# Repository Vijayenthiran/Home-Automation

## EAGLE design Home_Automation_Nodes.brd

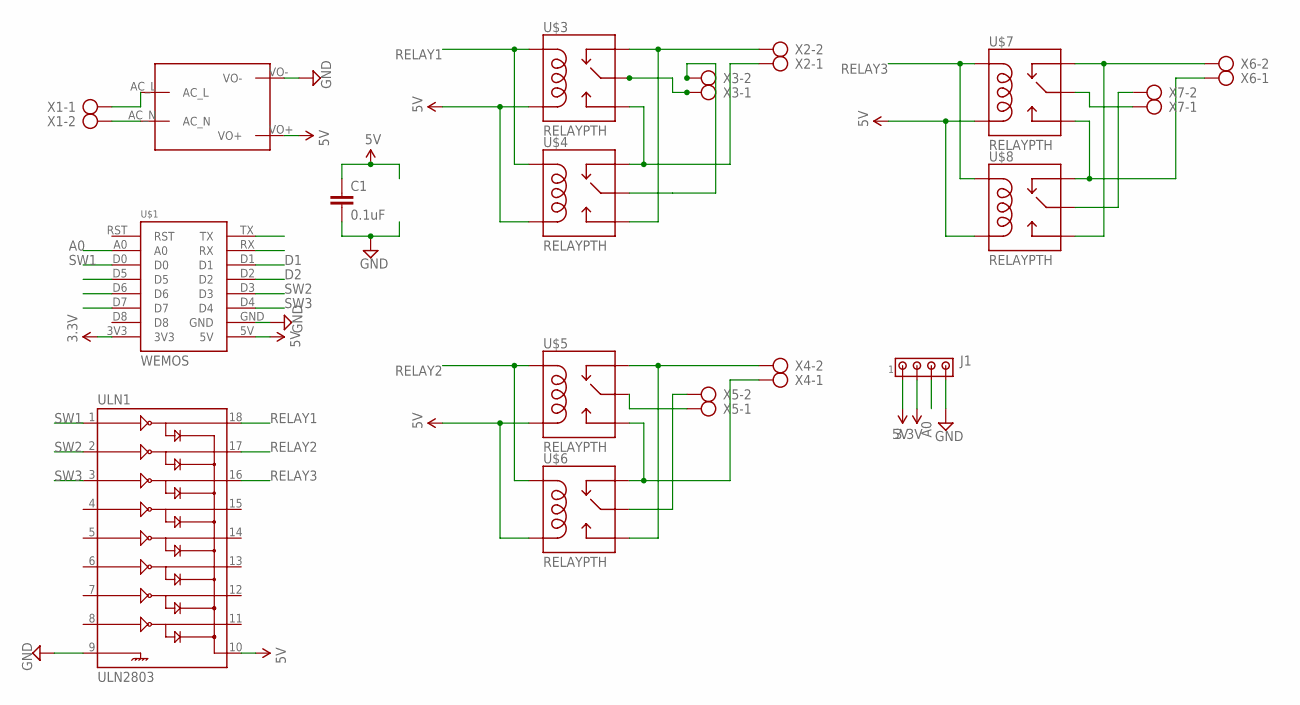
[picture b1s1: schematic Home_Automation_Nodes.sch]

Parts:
C1: 0.1uF; C025-025X050
J1: MTA04-100; 10X04MTA
U$1: WEMOS
U$2: MAINS_CONVERTERS; HLK-PM01
U$3, U$4, U$5, U$6, U$7, U$8: RELAYPTH; SRD-05VDC-SL-C
ULN1: ULN2803; DIL18
X1, X2, X3, X4, X5, X6, X7: AK300/2

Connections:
3.3V: J1.2, U$1.3V3
5V: C1.1, J1.1, U$1.5V, U$2.VO+, U$3.COIL0, U$4.COIL0, U$5.COIL0, U$6.COIL0, U$7.COIL0, U$8.COIL0, ULN1.10
A0: J1.3, U$1.A0
D1: U$1.D1
D2: U$1.D2
D5: U$1.D5
D6: U$1.D6
D7: U$1.D7
GND: C1.2, J1.4, U$1.GND, U$2.VO-, ULN1.9
unnamed: U$2.AC_N, X1.2
unnamed: U$2.AC_L, X1.1
unnamed: U$3.SWCOMMON, X3.1
unnamed: U$5.SWCOMMON, X5.1
unnamed: U$3.SWOPEN, U$4.SWCLOSED (SWCLOSE), X2.1
unnamed: U$3.SWCLOSED (SWCLOSE), U$4.SWOPEN, X2.2
unnamed: U$7.SWCOMMON, X7.1
unnamed: U$4.SWCOMMON, X3.2
unnamed: U$5.SWOPEN, U$6.SWCLOSED (SWCLOSE), X4.1
unnamed: U$5.SWCLOSED (SWCLOSE), U$6.SWOPEN, X4.2
unnamed: U$6.SWCOMMON, X5.2
unnamed: U$7.SWOPEN, U$8.SWCLOSED (SWCLOSE), X6.1
unnamed: U$7.SWCLOSED (SWCLOSE), U$8.SWOPEN, X6.2
unnamed: U$8.SWCOMMON, X7.2
RELAY1: U$3.COIL1, U$4.COIL1, ULN1.18
RELAY2: U$5.COIL1, U$6.COIL1, ULN1.17
RELAY3: U$7.COIL1, U$8.COIL1, ULN1.16
SW1: U$1.D0, ULN1.1
SW2: U$1.D3, ULN1.2
SW3: U$1.D4, ULN1.3

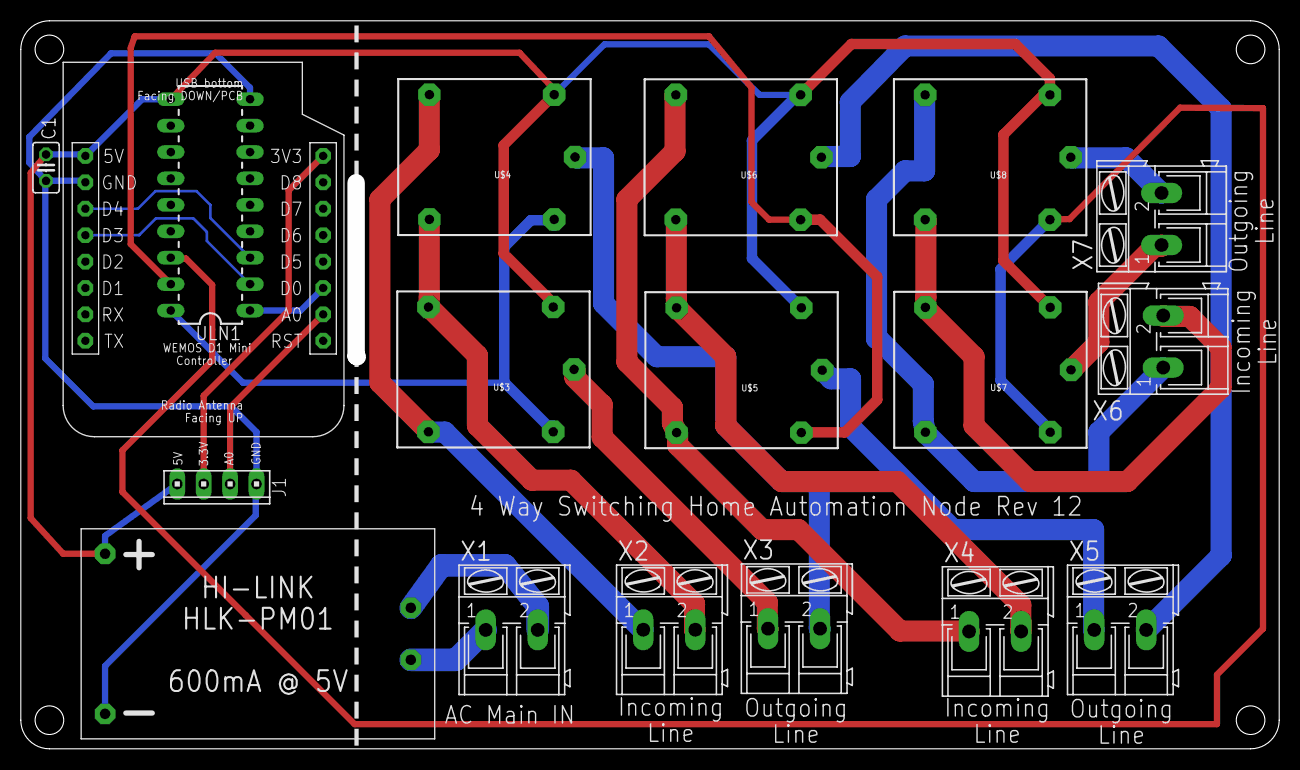
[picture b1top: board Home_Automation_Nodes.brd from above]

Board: 2 copper layers, 119.3 x 68.3 mm, 18 parts (0 on the bottom side), 24 nets.

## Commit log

2016-11-26 Board for 4 Channel Solid State Relay. 1. Includes Current sensor 5 inch cross 3 inch foorprint
2016-11-26 Initial Commit for 4 way switching configuration
2016-11-27 1. Rotated the WeMos position to expose the USB 2. 100% Routing with autorouter 3. Big pads for relays 4. Screw terminal fix for the first set of relays
2016-11-27 Removed a set of relay. Still routing
2016-11-30 Full DRC pass 1. There are few low priority dimension issue on the top right 2. The screw terminals are still considered as side entry. Need to cross verify with the top entry dimenstions
2016-12-01 Milling layer added. But looks bad
2016-12-02 100 mils spacing Top Bottom routing.No Vias
2016-12-03 Changes: 1. SCH: Added decoupling capacitor. Breakout for A0 and 4 digital pins 2. BRD: 100 mils spacing, 80 mils track width. Legends added
2016-12-07 Final version. Sent to Mervin for verification
2016-12-08 ULN connection fix. Changed coil connection from GND to 5V
2016-12-12 Changes: 1. WeMos D1 Mini Pads modified 2. Pins to ULN changed, to free the SPI channels 3. GND Plane added
2016-12-12 Silk Screen Fix. Sent for prod

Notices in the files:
parts and their libraries:
SparkFun-PowerIC: Licensing: Creative Commons ShareAlike 4.0 International - https://creativecommons.org/licenses/by-sa/4.0
